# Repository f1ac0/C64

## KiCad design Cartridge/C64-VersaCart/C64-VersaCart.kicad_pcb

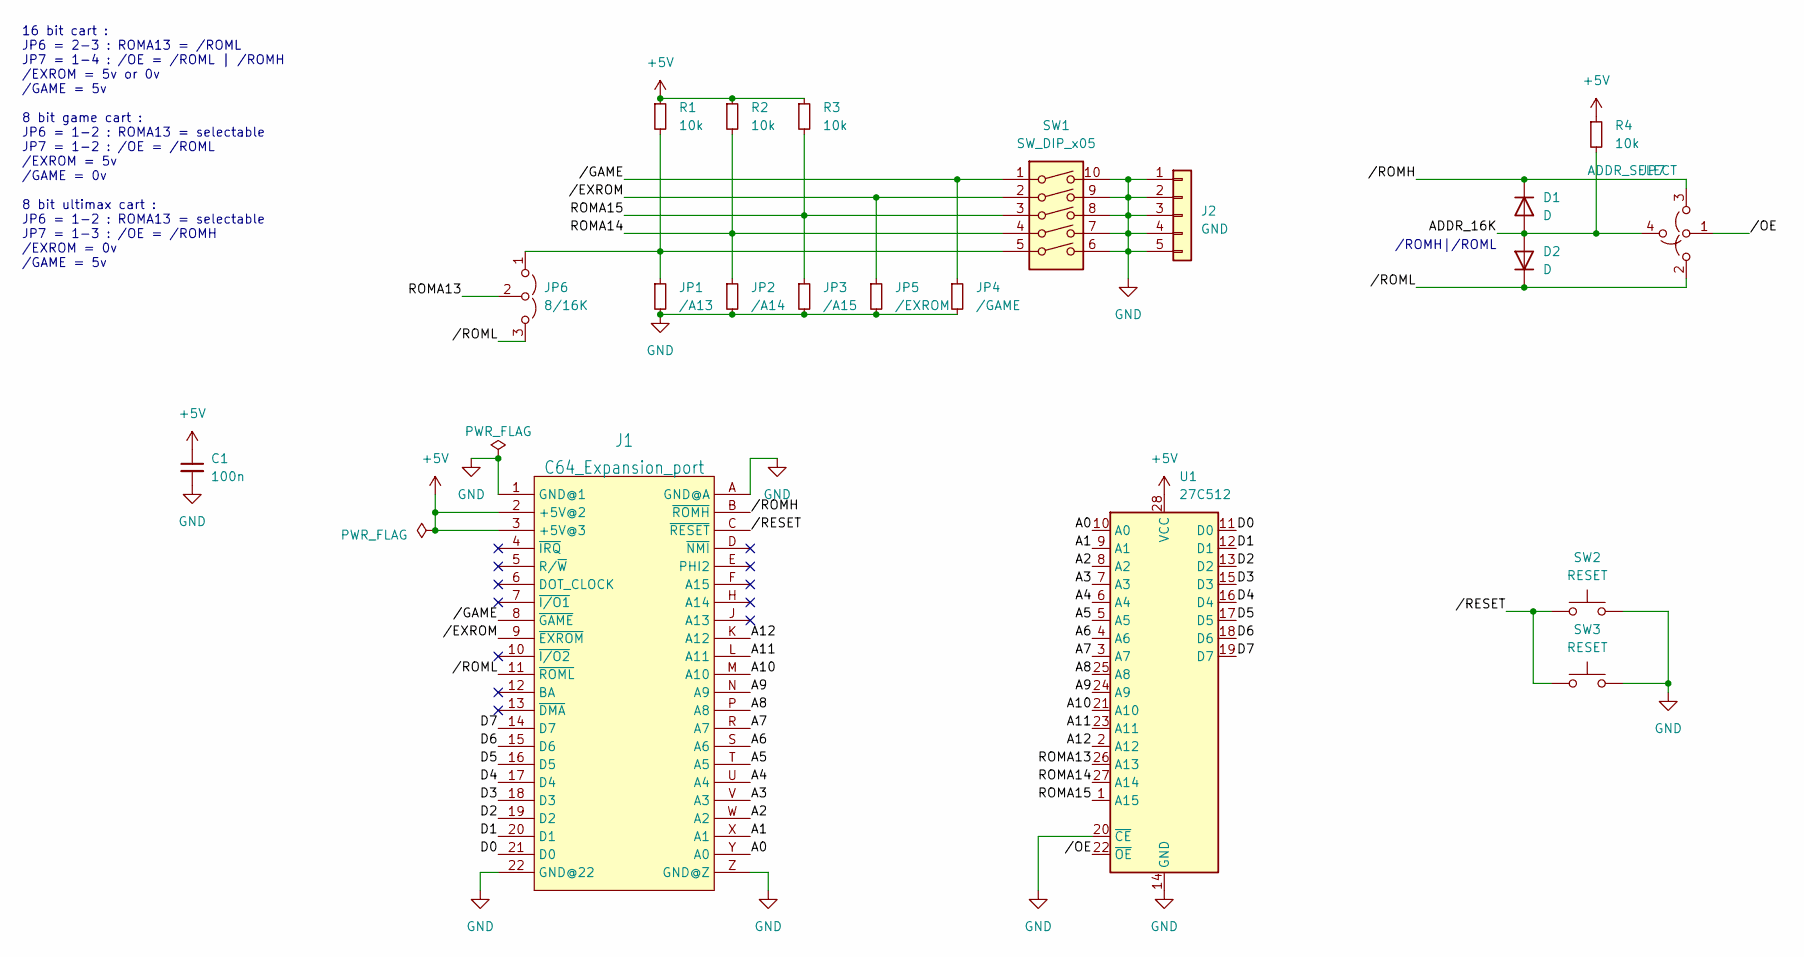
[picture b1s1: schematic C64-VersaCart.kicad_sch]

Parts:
C1: 100n; C_0805_2012Metric
D1, D2: D; D_0805_2012Metric
J1: C64_Expansion_port; C64_Expansion_2x22_2.54mm
J2: GND; PinHeader_1x05_P2.54mm_Vertical
JP1: /A13; SolderJumper-2_P1.3mm_Open_RoundedPad1.0x1.5mm
JP2: /A14; SolderJumper-2_P1.3mm_Open_RoundedPad1.0x1.5mm
JP3: /A15; SolderJumper-2_P1.3mm_Open_RoundedPad1.0x1.5mm
JP4: /GAME; SolderJumper-2_P1.3mm_Open_RoundedPad1.0x1.5mm
JP5: /EXROM; SolderJumper-2_P1.3mm_Open_RoundedPad1.0x1.5mm
JP6: 8/16K; Jumper_3_SPDT_P2.54mm_Vertical
JP7: ADDR_SELECT; Jumper_4_SPTT_P2.54mm_Vertical
R1, R2, R3: 10k; C_0805_2012Metric_shortable
R4: 10k; R_0805_2012Metric
SW1: SW_DIP_x05; SW_DIP_SPSTx05_Slide_9.78x14.88mm_W7.62mm_P2.54mm
SW2: RESET; SW_SPST_FSMSM
SW3: RESET; SW_PUSH_6mm
U1: 27C512; DIP-28_W15.24mm

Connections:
+5V: C1.1, J1.2 (+5V@2), J1.3 (+5V@3), R1.1, R2.1, R3.1, R4.1, U1.28 (VCC)
/A0: J1.Y (A0), U1.10 (A0)
/A1: J1.X (A1), U1.9 (A1)
/A2: J1.W (A2), U1.8 (A2)
/A3: J1.V (A3), U1.7 (A3)
/A4: J1.U (A4), U1.6 (A4)
/A5: J1.T (A5), U1.5 (A5)
/A6: J1.S (A6), U1.4 (A6)
/A7: J1.R (A7), U1.3 (A7)
/A8: J1.P (A8), U1.25 (A8)
/A9: J1.N (A9), U1.24 (A9)
/A10: J1.M (A10), U1.21 (A10)
/A11: J1.L (A11), U1.23 (A11)
/A12: J1.K (A12), U1.2 (A12)
/ADDR_16K: D1.2 (A), D2.2 (A), JP7.4 (D), R4.2
/D0: J1.21 (D0), U1.11 (D0)
/D1: J1.20 (D1), U1.12 (D1)
/D2: J1.19 (D2), U1.13 (D2)
/D3: J1.18 (D3), U1.15 (D3)
/D4: J1.17 (D4), U1.16 (D4)
/D5: J1.16 (D5), U1.17 (D5)
/D6: J1.15 (D6), U1.18 (D6)
/D7: J1.14 (D7), U1.19 (D7)
/ROMA13: JP6.2 (C), U1.26 (A13)
/ROMA14: JP2.1, R2.2, SW1.4, U1.27 (A14)
/ROMA15: JP3.1, R3.2, SW1.3, U1.1 (A15)
//EXROM: J1.9 (~EXROM), JP5.1, SW1.2
//GAME: J1.8 (~GAME), JP4.1, SW1.1
//OE: JP7.1 (A), U1.22 (~OE)
//RESET: J1.C (~RESET), SW2.1, SW3.1
//ROMH: D1.1 (K), J1.B (~ROMH), JP7.3 (B)
//ROML: D2.1 (K), J1.11 (~ROML), JP6.3 (B), JP7.2 (B)
GND: C1.2, J1.1 (GND@1), J1.22 (GND@22), J1.A (GND@A), J1.Z (GND@Z), J2.1, J2.2, J2.3, J2.4, J2.5, JP1.2, JP2.2, JP3.2, JP4.2, JP5.2, SW1.6, SW1.7, SW1.8, SW1.9, SW1.10, SW2.2, SW3.2, U1.14 (GND), U1.20 (~CE)
unnamed: JP1.1, JP6.1 (A), R1.2, SW1.5

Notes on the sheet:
/ROMH|/ROML
16 bit cart : JP6 = 2-3 : ROMA13 = /ROML JP7 = 1-4 : /OE = /ROML | /ROMH /EXROM = 5v or 0v /GAME = 5v 8 bit game cart : JP6 = 1-2 : ROMA13 = selectable JP7 = 1-2 : /OE = /ROML /EXROM = 5v /GAME = 0v 8 bit ultimax cart : JP6 = 1-2 : ROMA13 = selectable JP7 = 1-3 : /OE = /ROMH /EXROM = 0v /GAME = 5v

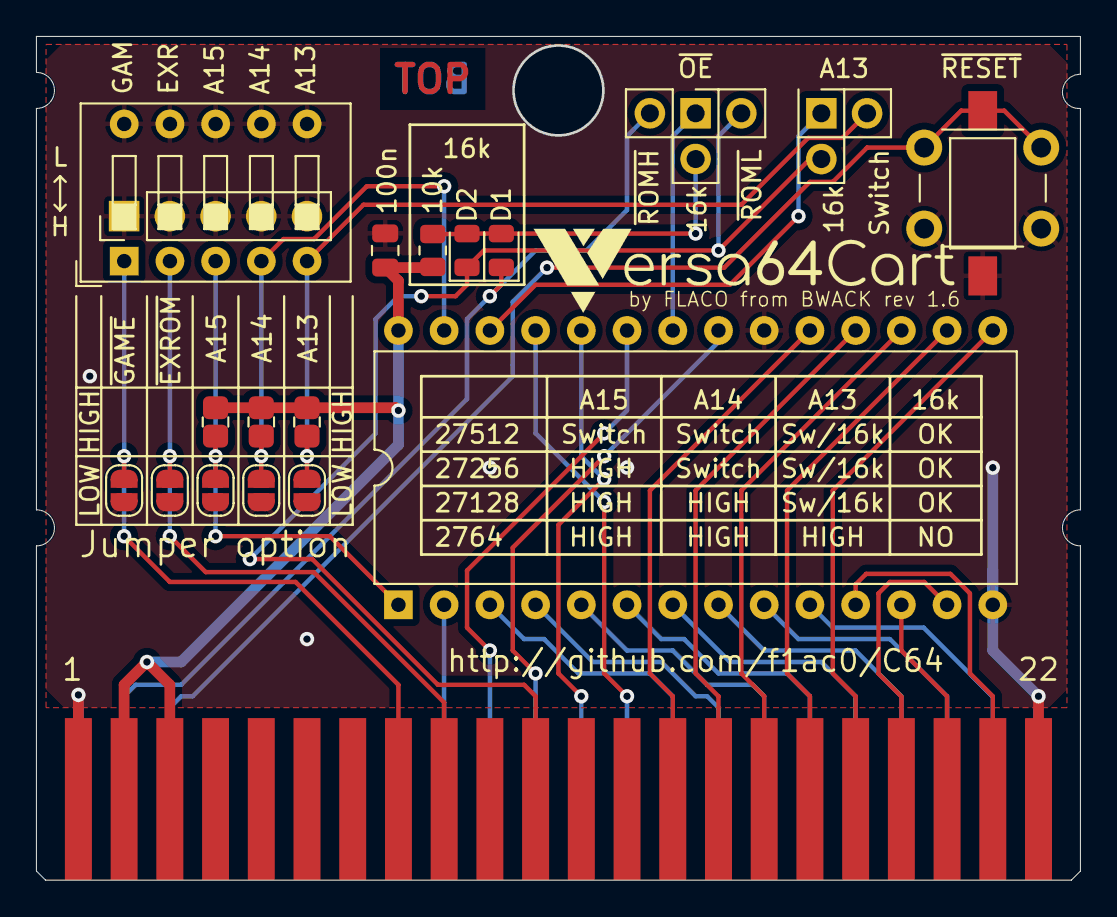
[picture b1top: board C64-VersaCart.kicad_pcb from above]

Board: 2 copper layers, 58.0 x 46.9 mm, 21 parts (0 on the bottom side), 34 nets.

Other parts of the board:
U$39: VERSA64CART

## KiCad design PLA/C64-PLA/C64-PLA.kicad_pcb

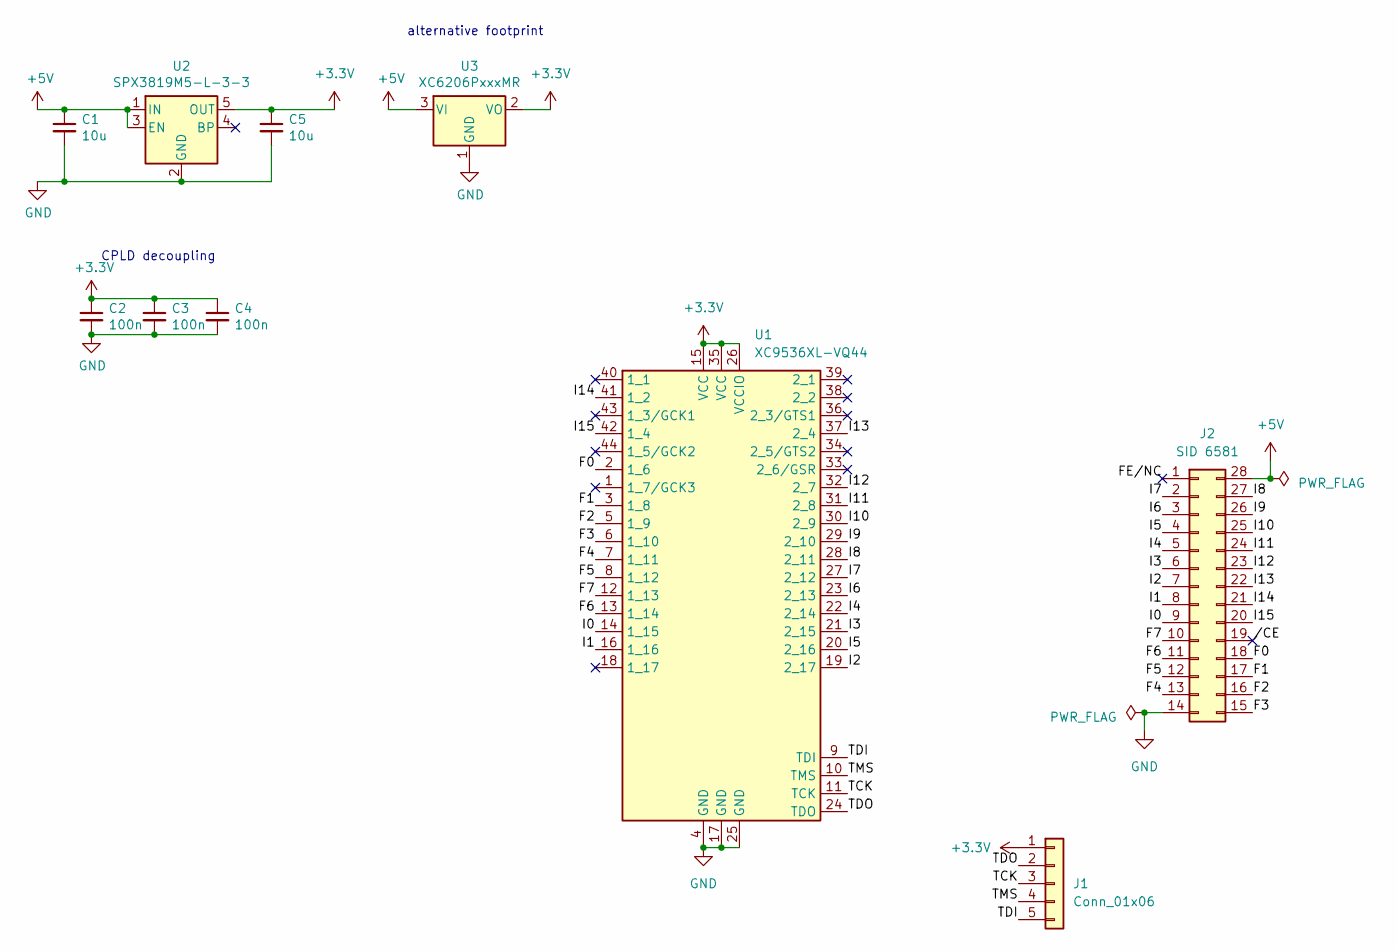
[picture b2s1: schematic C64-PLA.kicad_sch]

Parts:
C1, C5: 10u; C_0805_2012Metric
C2, C3, C4: 100n; C_0805_2012Metric
J1: Conn_01x06; PinHeader_1x05_P2.54mm_Vertical
J2: SID 6581; DIP-28_W15.24mm_BigPads1.4
U1: XC9536XL-VQ44; LQFP-44_10x10mm_P0.8mm
U2: SPX3819M5-L-3-3; SOT-23-5
U3: XC6206PxxxMR; SOT-23

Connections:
+3.3V: C2.1, C3.1, C4.1, C5.1, J1.1, U1.15 (VCC), U1.26 (VCCIO), U1.35 (VCC), U2.5 (OUT), U3.2 (VO)
+5V: C1.1, J2.28, U2.1 (IN), U2.3 (EN), U3.3 (VI)
/F0: J2.18, U1.2 (1_6)
/F1: J2.17, U1.3 (1_8)
/F2: J2.16, U1.5 (1_9)
/F3: J2.15, U1.6 (1_10)
/F4: J2.13, U1.7 (1_11)
/F5: J2.12, U1.8 (1_12)
/F6: J2.11, U1.13 (1_14)
/F7: J2.10, U1.12 (1_13)
/FE/NC: J2.1
/I0: J2.9, U1.14 (1_15)
/I1: J2.8, U1.16 (1_16)
/I2: J2.7, U1.19 (2_17)
/I3: J2.6, U1.21 (2_15)
/I4: J2.5, U1.22 (2_14)
/I5: J2.4, U1.20 (2_16)
/I6: J2.3, U1.23 (2_13)
/I7: J2.2, U1.27 (2_12)
/I8: J2.27, U1.28 (2_11)
/I9: J2.26, U1.29 (2_10)
/I10: J2.25, U1.30 (2_9)
/I11: J2.24, U1.31 (2_8)
/I12: J2.23, U1.32 (2_7)
/I13: J2.22, U1.37 (2_4)
/I14: J2.21, U1.41 (1_2)
/I15: J2.20, U1.42 (1_4)
/TCK: J1.3, U1.11 (TCK)
/TDI: J1.5, U1.9 (TDI)
/TDO: J1.2, U1.24 (TDO)
/TMS: J1.4, U1.10 (TMS)
//CE: J2.19
GND: C1.2, C2.2, C3.2, C4.2, C5.2, J2.14, U1.4 (GND), U1.17 (GND), U1.25 (GND), U2.2 (GND), U3.1 (GND)

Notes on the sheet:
CPLD decoupling
alternative footprint

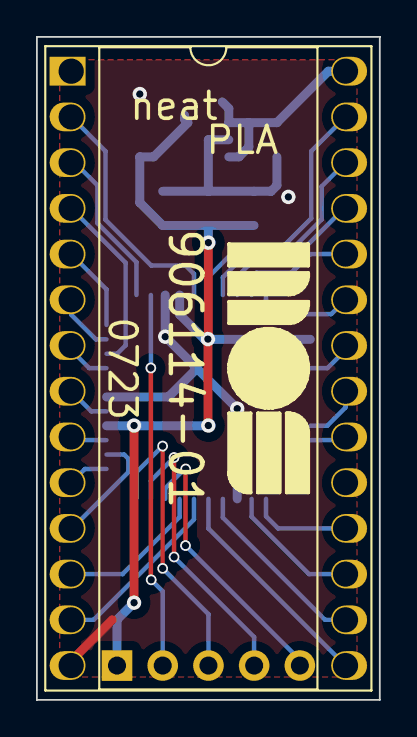
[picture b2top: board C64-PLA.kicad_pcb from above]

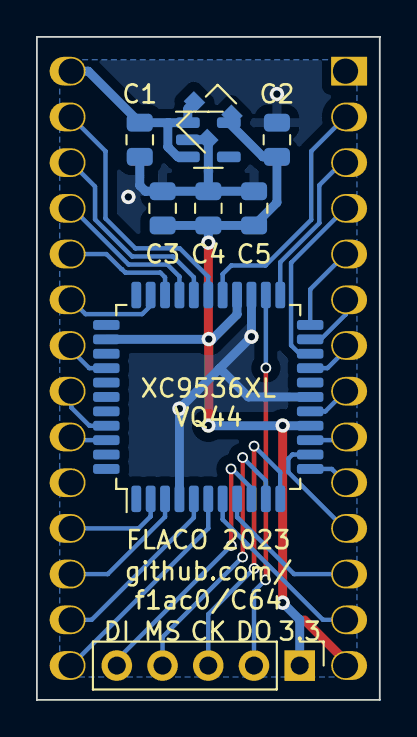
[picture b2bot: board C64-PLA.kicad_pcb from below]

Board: 2 copper layers, 19.0 x 36.8 mm, 10 parts (9 on the bottom side), 31 nets.

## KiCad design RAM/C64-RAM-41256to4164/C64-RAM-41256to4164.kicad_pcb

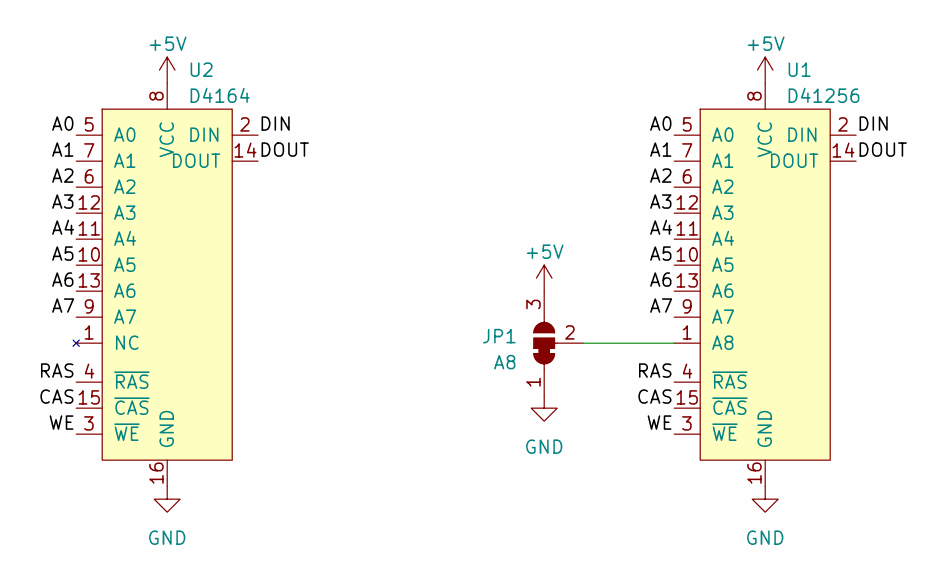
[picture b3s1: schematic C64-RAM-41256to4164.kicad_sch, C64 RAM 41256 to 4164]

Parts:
JP1: A8; SolderJumper-3_P1.3mm_Bridged12_RoundedPad1.0x1.5mm
U1: D41256; DIP-16_W7.62mm
U2: D4164; DIP-16_W7.62mm

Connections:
+5V: JP1.3 (B), U1.8 (VCC), U2.8 (VCC)
/A0: U1.5 (A0), U2.5 (A0)
/A1: U1.7 (A1), U2.7 (A1)
/A2: U1.6 (A2), U2.6 (A2)
/A3: U1.12 (A3), U2.12 (A3)
/A4: U1.11 (A4), U2.11 (A4)
/A5: U1.10 (A5), U2.10 (A5)
/A6: U1.13 (A6), U2.13 (A6)
/A7: U1.9 (A7), U2.9 (A7)
/CAS: U1.15 (~CAS), U2.15 (~CAS)
/DIN: U1.2 (DIN), U2.2 (DIN)
/DOUT: U1.14 (DOUT), U2.14 (DOUT)
/RAS: U1.4 (~RAS), U2.4 (~RAS)
/WE: U1.3 (~WE), U2.3 (~WE)
GND: JP1.1 (A), U1.16 (GND), U2.16 (GND)
unnamed: JP1.2 (C), U1.1 (A8)

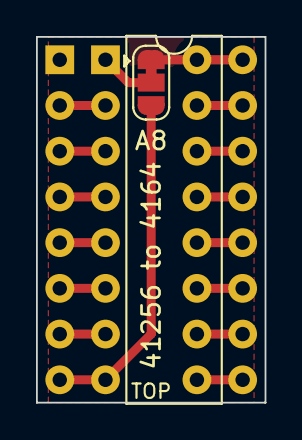
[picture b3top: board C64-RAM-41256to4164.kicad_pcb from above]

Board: 2 copper layers, 12.7 x 20.3 mm, 3 parts (0 on the bottom side), 16 nets.

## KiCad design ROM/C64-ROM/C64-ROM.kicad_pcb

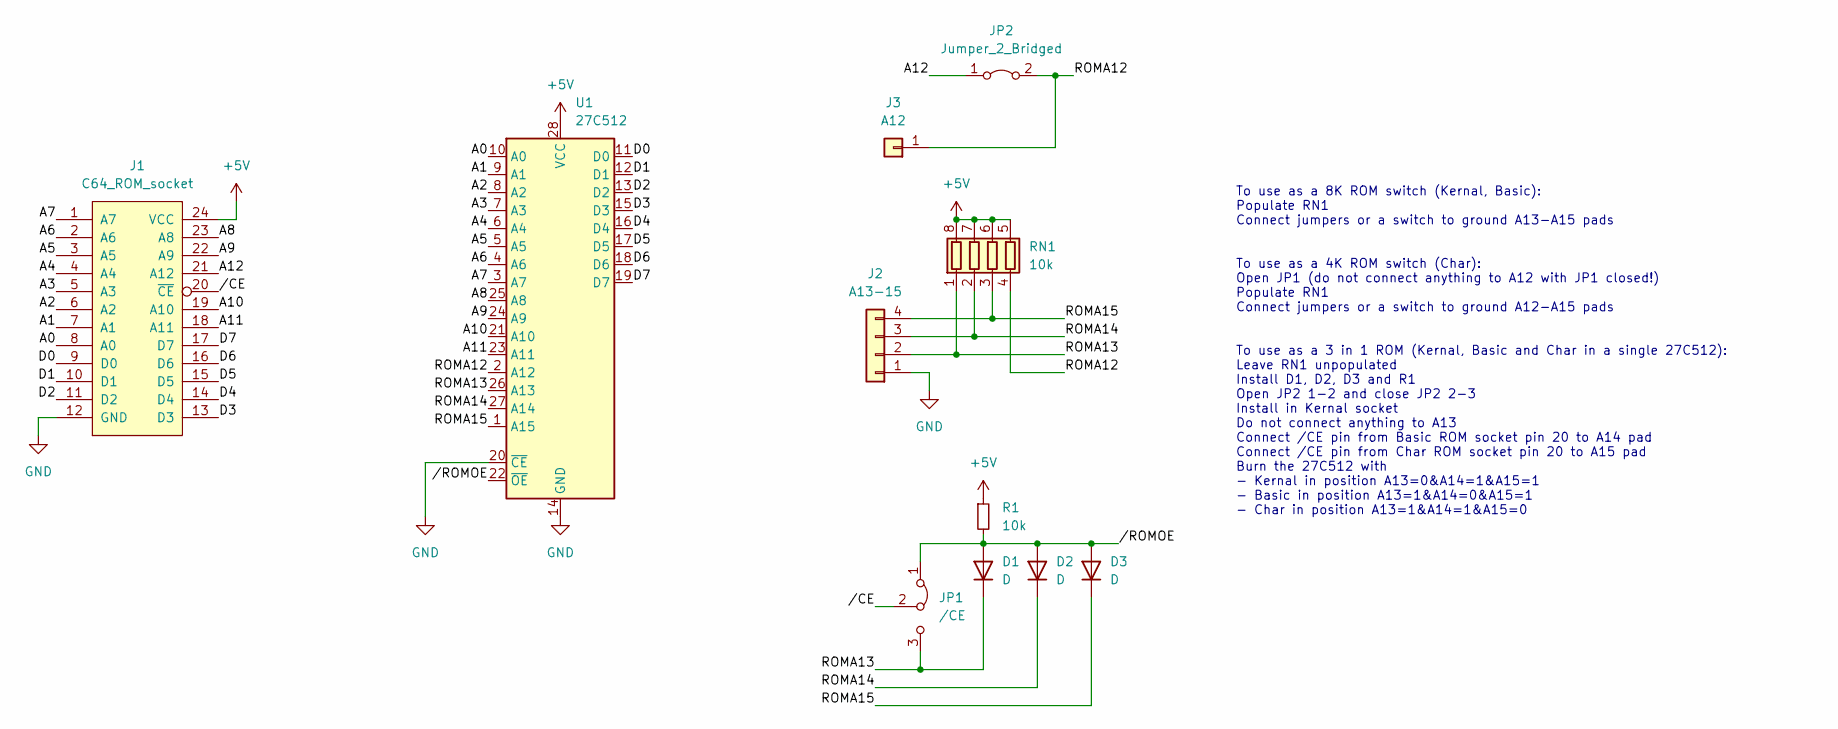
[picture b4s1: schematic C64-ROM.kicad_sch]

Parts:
D1, D2, D3: D; D_0805_2012Metric
J1: C64_ROM_socket; DIP-24_W15.24mm
J2: A13-15; PinHeader_1x04_P2.54mm_Vertical
J3: A12; TestPoint_THTPad_D1.7mm_Drill1.0mm
JP1: /CE; SolderJumper-3_P1.3mm_Bridged12_RoundedPad1.0x1.5mm_NumberL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
JP2: Jumper_2_Bridged; SolderJumper-2_P1.3mm_Bridged_RoundedPad1.0x1.5mm
R1: 10k; R_0805_2012Metric
RN1: 10k; R_Array_Convex_4x0603
U1: 27C512; DIP-28_W15.24mm

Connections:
+5V: J1.24 (VCC), R1.1, RN1.5 (R4.2), RN1.6 (R3.2), RN1.7 (R2.2), RN1.8 (R1.2), U1.28 (VCC)
/A0: J1.8 (A0), U1.10 (A0)
/A1: J1.7 (A1), U1.9 (A1)
/A2: J1.6 (A2), U1.8 (A2)
/A3: J1.5 (A3), U1.7 (A3)
/A4: J1.4 (A4), U1.6 (A4)
/A5: J1.3 (A5), U1.5 (A5)
/A6: J1.2 (A6), U1.4 (A6)
/A7: J1.1 (A7), U1.3 (A7)
/A8: J1.23 (A8), U1.25 (A8)
/A9: J1.22 (A9), U1.24 (A9)
/A10: J1.19 (A10), U1.21 (A10)
/A11: J1.18 (A11), U1.23 (A11)
/A12: J1.21 (A12), JP2.1 (A)
/D0: J1.9 (D0), U1.11 (D0)
/D1: J1.10 (D1), U1.12 (D1)
/D2: J1.11 (D2), U1.13 (D2)
/D3: J1.13 (D3), U1.15 (D3)
/D4: J1.14 (D4), U1.16 (D4)
/D5: J1.15 (D5), U1.17 (D5)
/D6: J1.16 (D6), U1.18 (D6)
/D7: J1.17 (D7), U1.19 (D7)
/ROMA12: J3.1, JP2.2 (B), RN1.4 (R4.1), U1.2 (A12)
/ROMA13: D1.1 (K), J2.2, JP1.3 (B), RN1.1 (R1.1), U1.26 (A13)
/ROMA14: D2.1 (K), J2.3, RN1.2 (R2.1), U1.27 (A14)
/ROMA15: D3.1 (K), J2.4, RN1.3 (R3.1), U1.1 (A15)
//CE: J1.20 (~CE), JP1.2 (C)
//ROMOE: D1.2 (A), D2.2 (A), D3.2 (A), JP1.1 (A), R1.2, U1.22 (~OE)
GND: J1.12 (GND), J2.1, U1.14 (GND), U1.20 (~CE)

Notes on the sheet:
To use as a 8K ROM switch (Kernal, Basic): Populate RN1 Connect jumpers or a switch to ground A13-A15 pads To use as a 4K ROM switch (Char): Open JP1 (do not connect anything to A12 with JP1 closed!) Populate RN1 Connect jumpers or a switch to ground A12-A15 pads To use as a 3 in 1 ROM (Kernal, Bas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

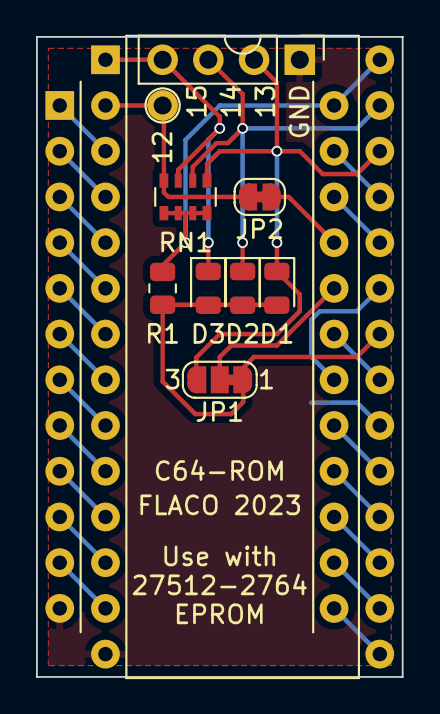
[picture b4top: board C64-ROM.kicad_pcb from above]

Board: 2 copper layers, 20.3 x 35.6 mm, 11 parts (0 on the bottom side), 29 nets.

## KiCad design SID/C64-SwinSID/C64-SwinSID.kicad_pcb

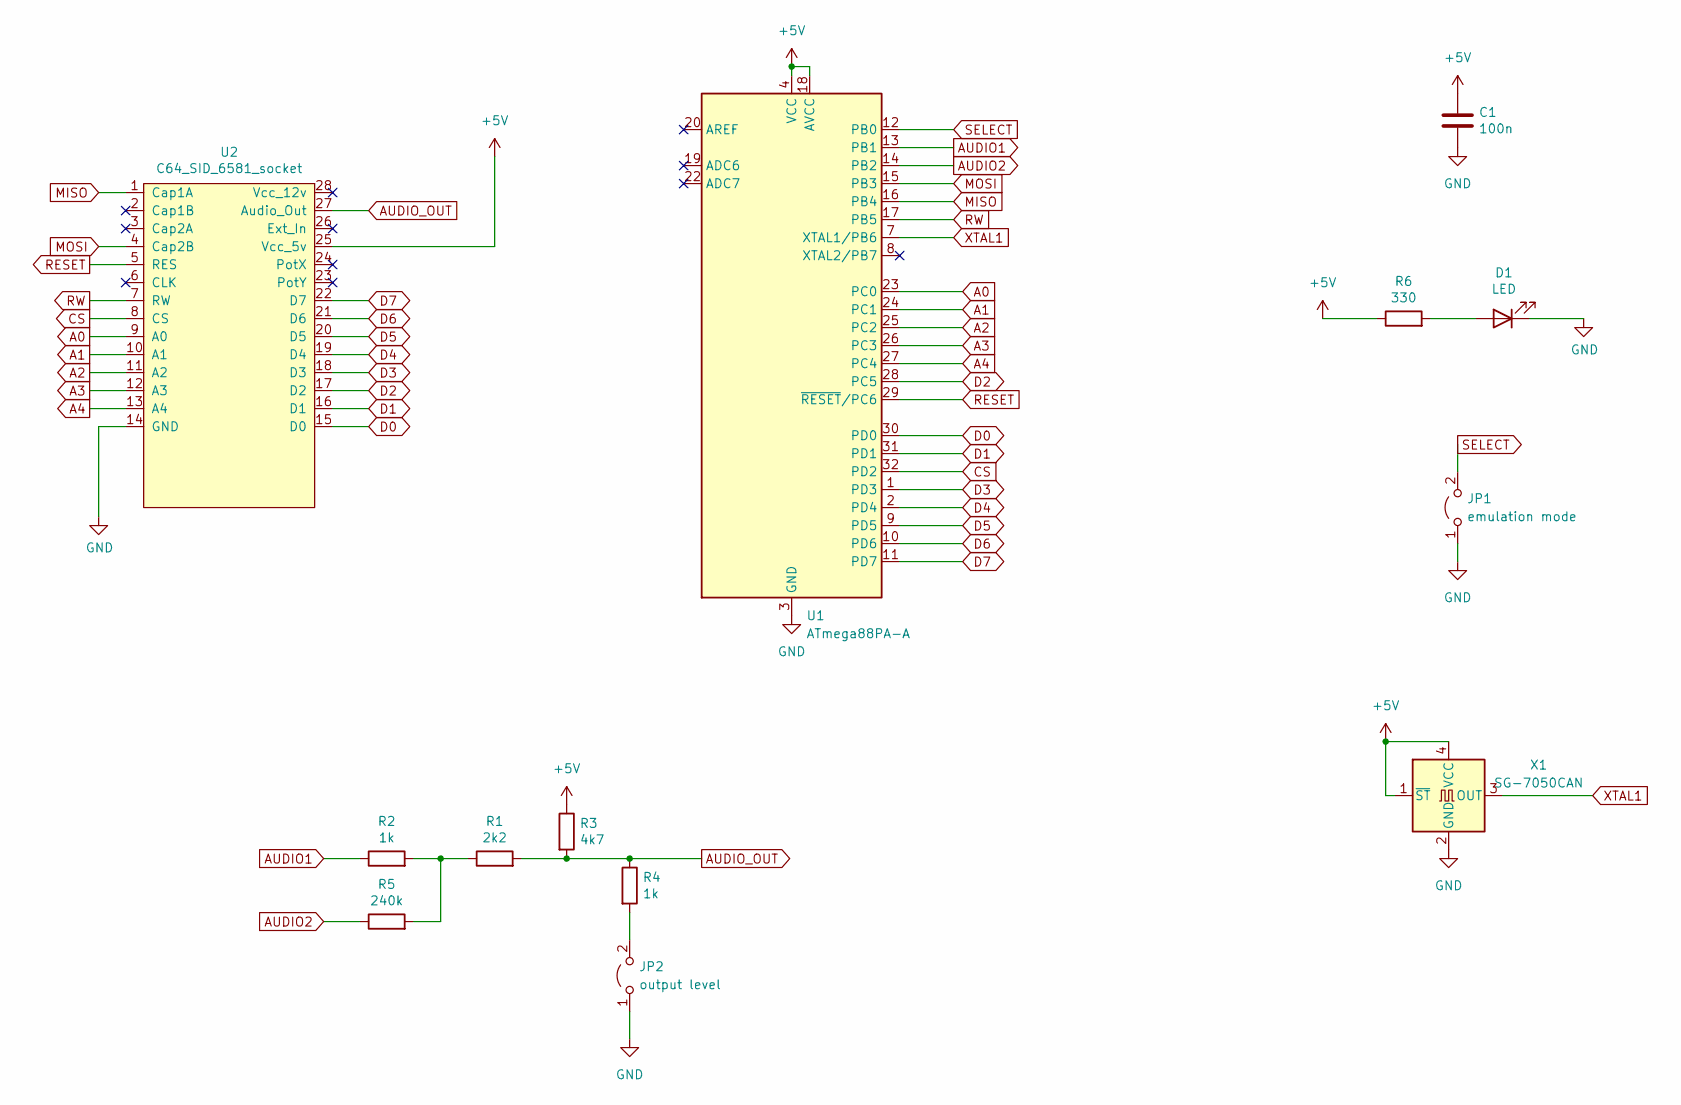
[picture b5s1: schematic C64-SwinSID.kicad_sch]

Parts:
C1: 100n; C_0805_2012Metric
D1: LED; LED_0805_2012Metric
JP1: emulation mode; PinHeader_1x02_P2.54mm_Vertical
JP2: output level; PinHeader_1x02_P2.54mm_Vertical
R1: 2k2; R_0805_2012Metric
R2, R4: 1k; R_0805_2012Metric
R3: 4k7; R_0805_2012Metric
R5: 240k; R_0805_2012Metric
R6: 330; R_0805_2012Metric
U1: ATmega88PA-A; TQFP-32_7x7mm_P0.8mm
U2: C64_SID_6581_socket; DIP-28_W15.24mm
X1: SG-7050CAN; Crystal_SMD_7050-4Pin_7.0x5.0mm

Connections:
+5V: C1.1, R3.1, R6.1, U1.4 (VCC), U1.6 (VCC), U1.18 (AVCC), U2.25 (Vcc_5v), X1.1 (~ST), X1.4 (VCC)
A0: U1.23 (PC0), U2.9 (A0)
A1: U1.24 (PC1), U2.10 (A1)
A2: U1.25 (PC2), U2.11 (A2)
A3: U1.26 (PC3), U2.12 (A3)
A4: U1.27 (PC4), U2.13 (A4)
AUDIO1: R2.1, U1.13 (PB1)
AUDIO2: R5.1, U1.14 (PB2)
AUDIO_OUT: R1.2, R3.2, R4.1, U2.27 (Audio_Out)
CS: U1.32 (PD2), U2.8 (CS)
D0: U1.30 (PD0), U2.15 (D0)
D1: U1.31 (PD1), U2.16 (D1)
D2: U1.28 (PC5), U2.17 (D2)
D3: U1.1 (PD3), U2.18 (D3)
D4: U1.2 (PD4), U2.19 (D4)
D5: U1.9 (PD5), U2.20 (D5)
D6: U1.10 (PD6), U2.21 (D6)
D7: U1.11 (PD7), U2.22 (D7)
GND: C1.2, D1.1 (K), JP1.1 (A), JP2.1 (A), U1.3 (GND), U1.5 (GND), U1.21 (GND), U2.14 (GND), X1.2 (GND)
MISO: U1.16 (PB4), U2.1 (Cap1A)
MOSI: U1.15 (PB3), U2.4 (Cap2B)
unnamed: R1.1, R2.2, R5.2
unnamed: JP2.2 (B), R4.2
unnamed: D1.2 (A), R6.2
RESET: U1.29 (~RESET/PC6), U2.5 (RES)
RW: U1.17 (PB5), U2.7 (RW)
SELECT: JP1.2 (B), U1.12 (PB0)
XTAL1: U1.7 (XTAL1/PB6), X1.3 (OUT)

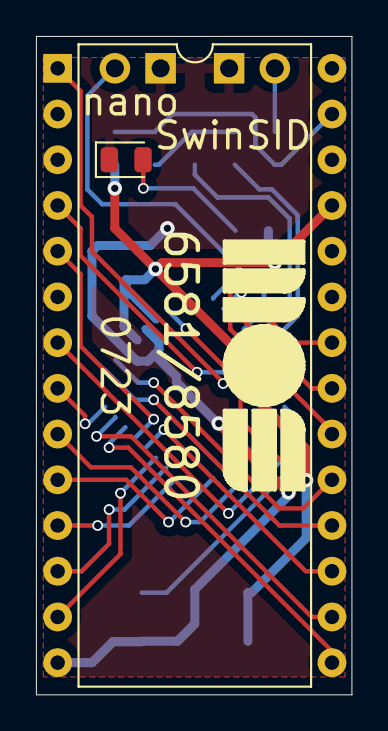
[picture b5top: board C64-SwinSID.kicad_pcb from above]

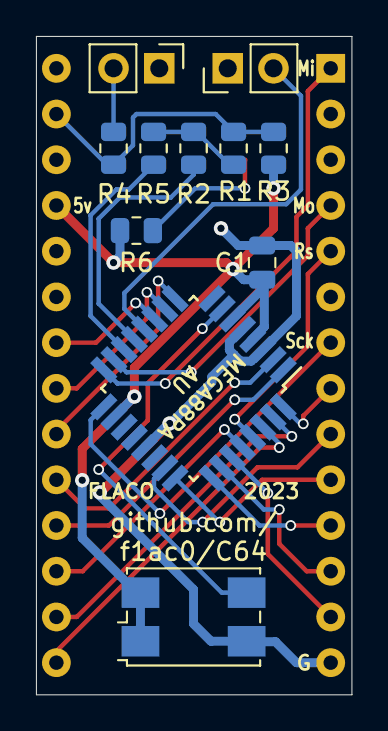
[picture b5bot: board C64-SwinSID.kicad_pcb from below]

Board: 2 copper layers, 17.5 x 36.6 mm, 13 parts (11 on the bottom side), 28 nets.

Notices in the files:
RAM/C64-RAM-41256to4164/C64-RAM-41256to4164.kicad_pcb:
CC-BY-NC-SA 4.0
